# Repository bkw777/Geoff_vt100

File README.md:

# Geoff's VT100 Terminal  
BKW respin, NOT WORKING, needs Firmware.  

PCB from OSHPark: <https://oshpark.com/shared_projects/MvDzzk9e>  
Parts from Digi-Key: <https://www.digikey.com/short/zrdw9v>

## Credits  
This version aims to combine elements from the following other versions:  

* [Geoff Graham](https://geoffg.net/terminal.html)  
 The original version  
* [Peter Hizalev](https://github.com/petrohi/terminal)  
 "v2.0" with rearranged PCB and modified firmware  
* [David Hansel](https://github.com/dhansel/TerminalUSB)   
 USB keyboard instead of PS/2  

## Goal  
Changes in this version:
 - remove ps/2 port
 - change usb port to type-a female
 - barrel power jack
 - remove all GND traces
 - add copper pours for GND on both sides
 - optimize routes, increase clearances, and tweak footprints to get full copper pour coverage  
 - DigiKey BOM  
 - Fully self-contained KiCAD files  

## Status  
 PCB: done but not tested  
  need to clean out un-used components and models  
  need to include a few more symbols & footprints  

 Firmware: has not been touched at all yet. Firmware probably does not work currently, as it is just a copy of Peter Hizalev's firmware, but the PCB no longer matches that PCB.  
  Peter Hizalev PCB uses a 20mhz crystal, which this PCB has  
  This PCB started from Peter's, so if the firmware requires any other hardware differences, like different pinout to the mcu, this board should match  
  Peter Hizalev firmware expects keyboard on PS/2, which this PCB does not have  

 TODO:  
  Generate diffs between the 3 source versions above to understand the changes each made vs the original  
  Combine Peter Hizalev and David Hansel changes

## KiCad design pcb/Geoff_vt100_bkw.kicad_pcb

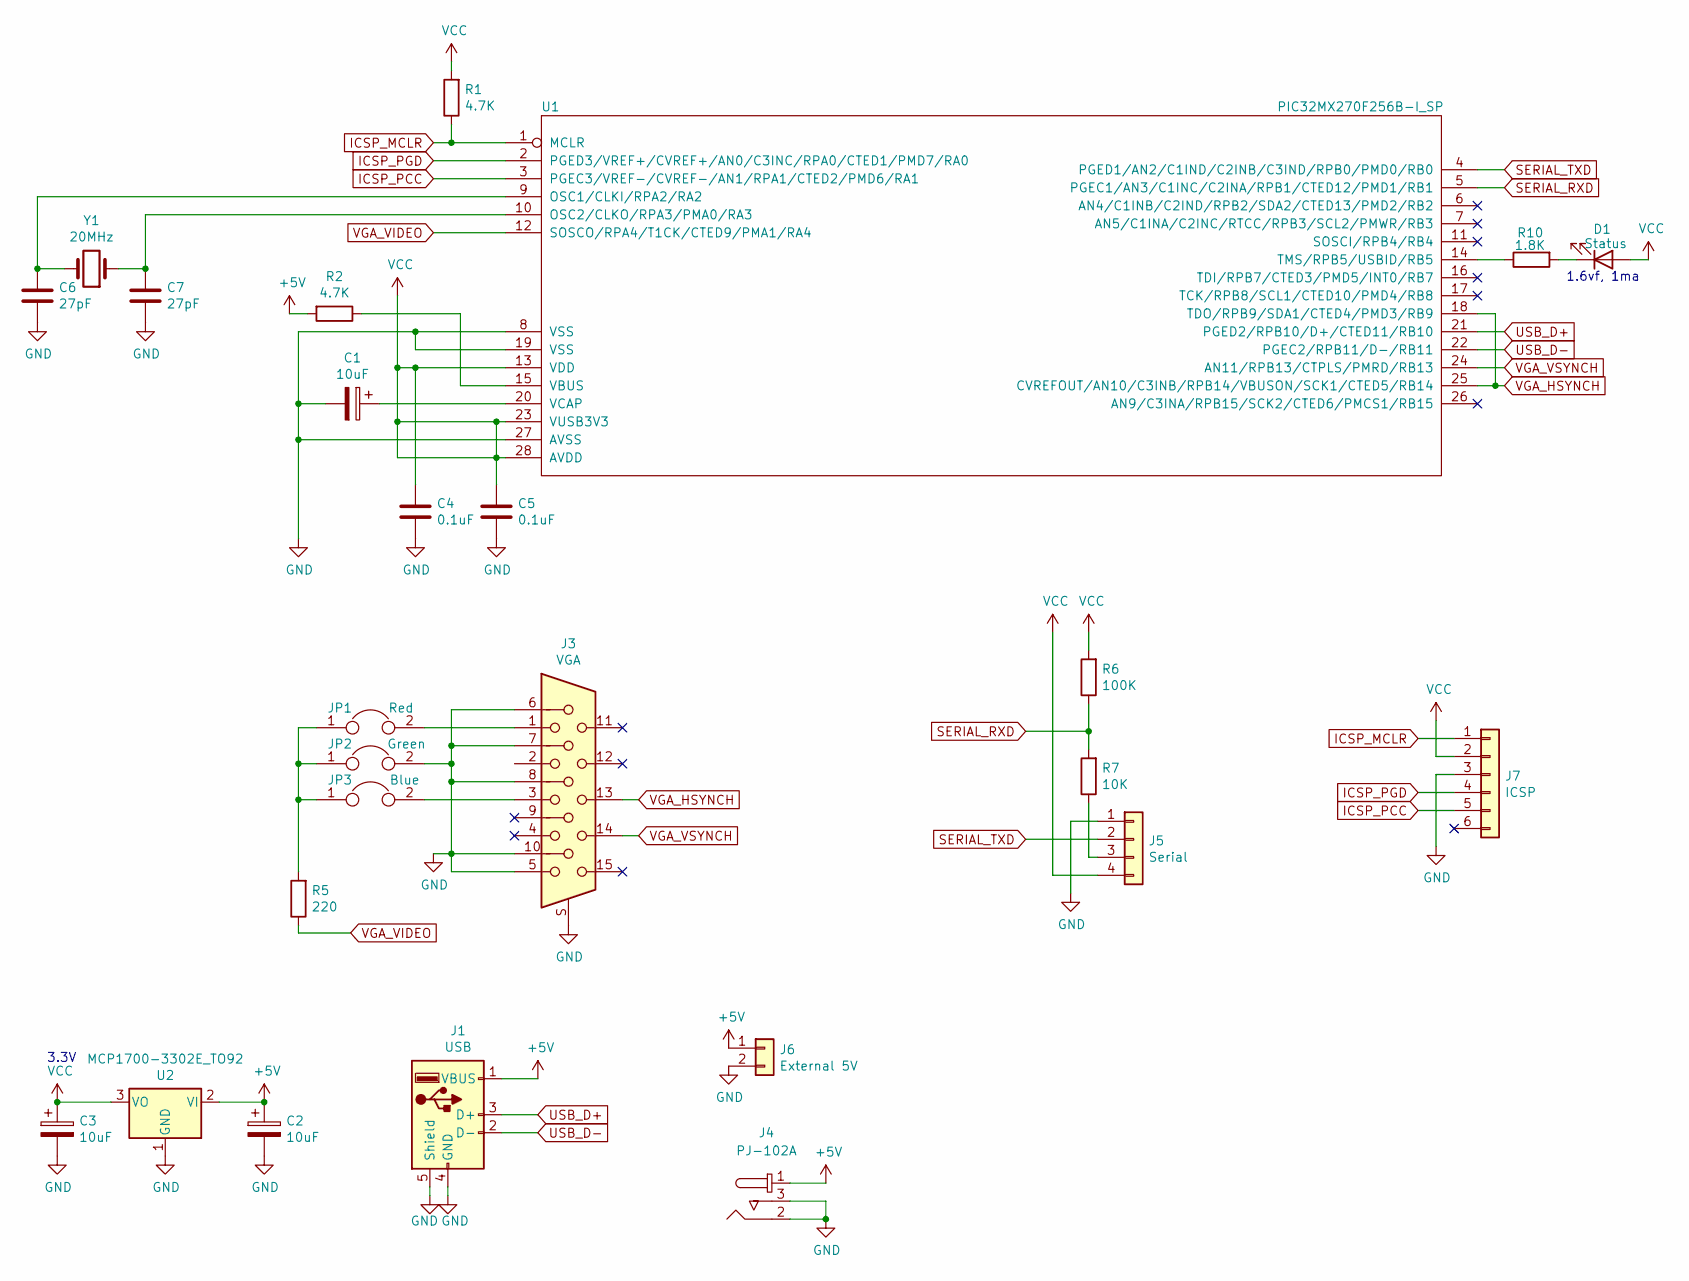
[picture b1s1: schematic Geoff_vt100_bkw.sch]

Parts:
C1, C2, C3: 10uF; CP_Radial_Tantal_D5.0mm_P5.00mm
C4, C5: 0.1uF; C_Disc_D5.0mm_W2.5mm_P5.00mm
C6, C7: 27pF; C_Disc_D5.0mm_W2.5mm_P5.00mm
D1: Status; LED_D5.0mm
J1: USB; USB_A_Female_UE27AC54100
J3: VGA; ICD15S13E4GX00LF
J4: PJ-102A; Barrel_Jack_5.5mmODx2.1mmID_PJ-102A; MPN PJ-102A; Digi-Key_PN CP-102A-ND
J5: Serial; TE_3-641215-4
J6: External 5V; TE_3-641215-2
J7: ICSP; Pin_Header_Straight_1x06_Pitch2.54mm
JP1: Red; Pin_Header_Straight_1x02_Pitch2.54mm
JP2: Green; Pin_Header_Straight_1x02_Pitch2.54mm
JP3: Blue; Pin_Header_Straight_1x02_Pitch2.54mm
R1, R2: 4.7K; R_Axial_DIN0207_L6.3mm_D2.5mm_P7.62mm_Horizontal
R5: 220; R_Axial_DIN0207_L6.3mm_D2.5mm_P7.62mm_Horizontal
R6: 100K; R_Axial_DIN0207_L6.3mm_D2.5mm_P7.62mm_Horizontal
R7: 10K; R_Axial_DIN0207_L6.3mm_D2.5mm_P7.62mm_Horizontal
R10: 1.8K; R_Axial_DIN0207_L6.3mm_D2.5mm_P7.62mm_Horizontal
U1: PIC32MX270F256B-I_SP; DIP-28_W7.62mm_Socket
U2: MCP1700-3302E_TO92; TO-92_HandSolder
Y1: 20MHz; Crystal_HC49-4H_Vertical

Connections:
+5V: C2.1, J1.1 (VBUS), J4.1, J6.1, R2.2, U2.2 (VI)
ICSP_MCLR: J7.1, R1.1, U1.1 (MCLR)
ICSP_PCC: J7.5, U1.3 (PGEC3/VREF-/CVREF-/AN1/RPA1/CTED2/PMD6/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)
ICSP_PGD: J7.4, U1.2 (PGED3/VREF+/CVREF+/AN0/C3INC/RPA0/CTED1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)
unnamed: C1.1, U1.20 (VCAP)
unnamed: C6.1, U1.9 (OSC1/CLKI/RPA2/RA2), Y1.2
unnamed: C7.1, U1.10 (OSC2/CLKO/RPA3/PMA0/RA3), Y1.1
unnamed: D1.1 (K), R10.2
unnamed: J3.1, JP1.2
unnamed: J3.3, JP3.2
unnamed: J5.3, R7.1
unnamed: JP1.1, JP2.1, JP3.1, R5.2
unnamed: R2.1, U1.15 (VBUS)
unnamed: R10.1, U1.14 (TMS/RPB5/USBID/RB5)
SERIAL_RXD: R6.1, R7.2, U1.5 (PGEC1/AN3/C1INC/C2INA/RPB1/CTED12/PMD1/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)
SERIAL_TXD: J5.2, U1.4 (PGED1/AN2/C1IND/C2INB/C3IND/RPB0/PMD0/R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)
USB_D+: J1.3 (D+), U1.21 (PGED2/RPB10/D+/CTED11/RB10)
USB_D-: J1.2 (D-), U1.22 (PGEC2/RPB11/D-/RB11)
VCC: C3.1, C4.1, C5.1, D1.2 (A), J5.4, J7.2, R1.2, R6.2, U1.13 (VDD), U1.23 (VUSB3V3), U1.28 (AVDD), U2.3 (VO)
VGA_HSYNCH: J3.13, U1.18 (TDO/RPB9/SDA1/CTED4/PMD3/RB9), U1.25 (CVREFOUT/AN10/C3INB/RPB14/VBUSON/SCK1/C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)
VGA_VIDEO: R5.1, U1.12 (SOSCO/RPA4/T1CK/CTED9/PMA1/RA4)
VGA_VSYNCH: J3.14, U1.24 (AN11/RPB13/CTPLS/PMRD/RB13)

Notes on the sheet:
3.3V
1.6vf, 1ma

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
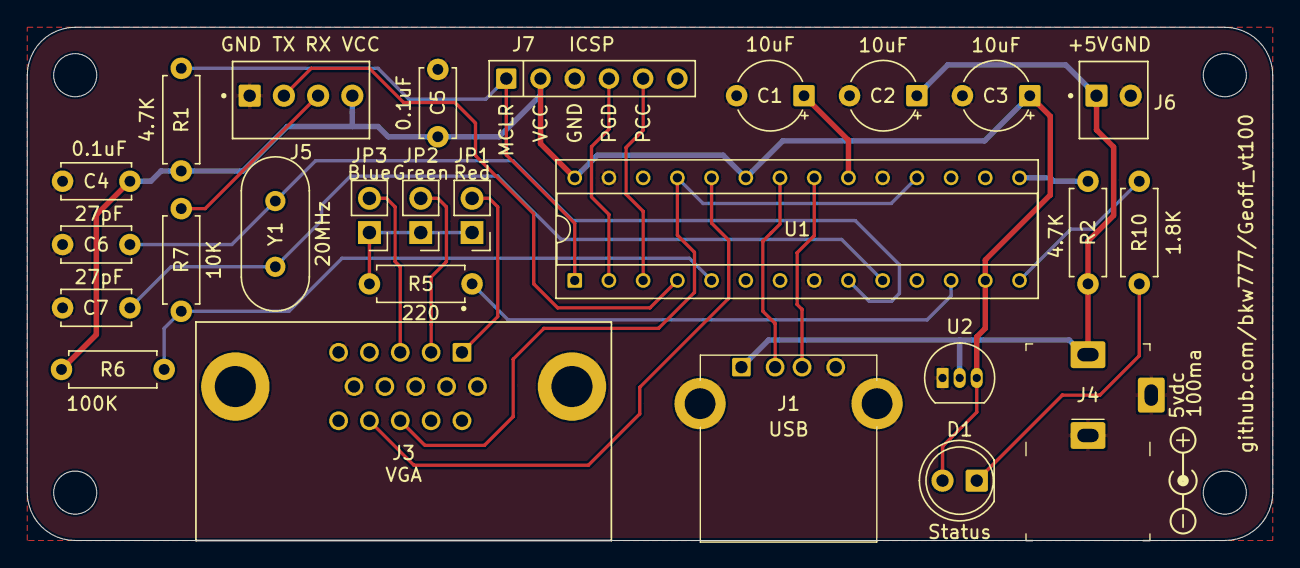
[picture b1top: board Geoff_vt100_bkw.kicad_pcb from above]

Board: 2 copper layers, 92.5 x 38.1 mm, 26 parts (0 on the bottom side), 24 nets.

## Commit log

2020-08-20 ground planes instead of traces, fatter traces for power
2020-08-22 footprint tweaks
2020-08-22 rename, add oshpark and digikey links
2020-08-25 usb keyboard, barrel power
2020-08-25 readme
2020-08-29 usb keyboard
